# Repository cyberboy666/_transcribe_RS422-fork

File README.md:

# \_transcribe_RS422-fork\_

### midi to _rs422_ bridge - for performance control of other old video mixers and switchers

### a fork of the existing [_transcribe_](https://github.com/cyberboy666/_transcribe_) project to experiment with rs422 - an alternative serial protocol

as discussed in this [github issue](https://github.com/cyberboy666/_transcribe_/issues/7) - the basic idea for this fork is to replace the max232 ic on transcribe with a max485 ic and experiment with a alternative version that will output rs422 serial instead. 

ultimitately this fork could be merged into the mainline by way of a _transcribe_ circuit revision that allows both protocols or adds the option for this extension circuit to be connected

panasonic mx20 is an example of a video mixer that could be controlled over rs422 serial - it expects it over (the rather uncommon) mini-din socket

the panasonic mx50 i believe can take either rs232 or rs422 on its din9 sefrial socket (selectable by a switch) this could be a good way for me to test the circuit myself

## main _transcribe_ readme

<details><summary>readme from original version of _transcribe_</summary>

### midi to rs232 bridge - for performance control of old video mixers and switchers

- this circuit is distributed by __UNDERSCORES__ - _an open video hardware label_ : it is available to purchase - as a pcb, kit or assembled unit - at [underscores.shop](https://underscores.shop/_transcribe_/)
- the schematic for the circuit can be found [here](/hardware/schematic.pdf)
- the pcb gerber files for the lastest version can be found [here](/hardware/gerber_latest.zip)
- consider [donating](https://liberapay.com/underscores/) to the underscores project to help us continue creating for the commons

## description

people in the video-art community are performing with old hardware video-mixers such as the Pansonic_WJ_AVE55 and Pansonic_WJ_MX30/50. some of these mixers have a RS232 serial port for interfacing with them digitally. this is especially useful for live performance where sequencing can assist physical actions. there are some cool examples of software specifically written to interface with these mixers (such as [Freds excel app](https://a2m2.ch/fred/wj-ave55.htm) and  [Klifs MaxPatch](https://vimeo.com/161662975) ) , but there many more programs and devices that are made to interface digitally using MIDI.

the aim of this project is to create a small utility module that can __\_transcribe\___ _MIDI_, a protocol used commonly in live&performance instruments to the specific _RS-232 video-device specification_ , to better equip these retired workstations for their new life of glamour on stage

- input USB-midi from a USB-HOST such as a computer or rpi
- input serial-midi from older midi devices (din5)
- input USB-midi for a USB-DEVICE such as a korg nanokontroller or otherwise
- output RS232-serial commands over 3.5mm jack or dsub9 socket to control panasonic video-mixers and other devices
- all these interfaces are bi-directional and so can be modified with firmware to do other useful things (eg like a USB-DEVICE -> SERIAL midi converter)

## demo video

# documentation

this project is fully _open-source hardware_ - all the files required to build it are included in this repo for free. if you have the time and/or skill you can contribute back by collaborating on / testing new designs, improving these docs, making demo videos/other creative content etc. you can also support the project financially by [donating directing](https://liberapay.com/underscores/), or purchasing through the [web shop](https://underscores.shop).

depending on whether you are going fully diy or buying an assembled and tested unit, some of the following guides will be relavent to you. the flow would be:

## ordering parts

<details><summary><b>parts sourcing guide (w/ notes on pcb fabracation )</b> - start here if you are building fully from scatch or have purchased a pcb</summary>

i try to source all the parts i can from either:
- [tayda](https://www.taydaelectronics.com/) ; cheaper for common parts like resistors etc, also good for mechanical parts like switches and buttons
- [mouser](https://www.mouser.de/) ; has lots more options, speciality video ic's, can sometimes cost more (free shipping on orders over 50euros)
- other ; ocationally there will be parts which will need to be sourced elsewhere - usaully either aliexpress, ebay or amazon etc...

take a look at the [full_bom](/hardware/bom/full_bom.csv) for this project to see where i am sourcing each part from
  
## omitting parts
  
if you know exactly how you will use your _transcribe_ some parts of this circuit build can be omitted. the pcb is divided into sections that are marked on silk-screen:

- __A - micro-conntroller - centre__ : this is the brain of the circuit and is required to make it do anything. its also where USB_MIDI is received from(/sent to) usb-hosts (eg computer or raspberry pi)
- __B - rs232 serial - output(/input)__ : for sending(/receiving) serial at rs232 levels - only omit if you are not using this board for its default / intended purpose
- __C - serial midi - input(/output)__ : for receiving(/sending) midi messages over serial (usually on older hardware over din5 or 3.5mm jack) - can omit if you are only using (newer) hardware with USB-MIDI
- __D USB-midi HOST__: adds circuitry so that micro-controller can act as USB-HOST. for receiving midi messages from(/sending to) usb-devices (eg korg nanokontrol2) - can omit this if not interested in controlling from usb-devices

## import into tayda

- go to the [tayda quick order](https://www.taydaelectronics.com/quick-order/) and in bottom corner choose _add from file_
- select the file [tayda_bom.csv](../hardware/bom/tayda_bom.csv) in the BOM folder (you will have to download it first or clone this repo)
- after importing select _add to cart_
- __NOTE:__ the minimum value for resistors is 10, so you may need to modify these values to add to cart (or if they are already modified here you will need to see the  full_bom for actual part QTY) 

- OPTIONAL: it is a good idea to add some dip-ic sockets and 2.54pin headers/sockets to your tayda order if you dont have them around already
  
## import into mouser

- go to [mouser bom tool](https://nz.mouser.com/Bom/) and click _upload spreadsheet_
- select the file [mouser_bom.csv](../hardware/bom/mouser_bom.csv) in this folder (you will have to download it first or clone this repo), then _upload my spreadsheet_ and _next_
- ensure that __Mouser Part Number__ is selected in the dropdown above the first row, then _next_, _process_
- if everything looks correct can now put _add to basket_

# ordering pcbs

you can support this project by buying individual pcbs from the [shop](https://underscores.shop). if you would rather have pcbs fabricated from gerbers directly the file you need is [here](/hardware/gerber_latest.zip) 

- i get my pcbs fabricated from [jlcpcb](https://cart.jlcpcb.com/quote) - 5 is the minumum order per design
- upload the zip file with the `add gerber file` button
- the default settings are mostly fine - set the __PCB Qty__ and __PCB Color__ settings (you can check that the file looks correct with pcb veiwer)
- it may be best to combine orders with other pcbs you want to have fab'd since the shipping can cost more than the items - also orginising group buys is a good way to distribute the extra pcbs /costs 
  
i often use jlcpcb because they are reliable, cheap and give you an option of colours. remember though that the cheapest Chinese fab houses are not always the most ethical or environmently friendly - if you can afford it consider supporting local companies. 

</details>

## assembly guide

<details><summary><b>assembly guide</b> - start here if you have purchased a diy kit</summary>

## interactive BOM for build guiding

follow this link to view the [interactive BOM](https://htmlpreview.github.io/?https://github.com/cyberboy666/_transcribe_/blob/main/hardware/bom/ibom.html)

## general solder advices

- remember to heat pad first (2-3seconds), then add solder, then continue to heat (1-2seconds)

- Checkout the web-comic [soldering is easy](https://mightyohm.com/files/soldercomic/FullSolderComic_EN.pdf) for more soldering advice

## general order of assembly

- in general while assembling i start placing resistors and capacitors first. placing 5 - 10 components at a time and then flipping the board to solder them and trim the legs etc.
- next i would do diodes, transistors and ic's - taking care that these are placed in the right direction (using a ic socket can be useful)
- finally i place the interface parts - rca jacks, power jack, pots and switches - make sure these have lots of solder on for structural stablity

## interface choice / double footprint
  
_serial-midi_ is most commonly sent over __din5__ (older hardware) J5 & J7 or __trs 3.5mm jack__ (newer hardware) J4 & J6 - footprints for both are overlayed on the pcb so you can choose which one you would like to have
  
## Usb-host shield

__IMPORTANT: A trace needs to be cut on the usb-host-shield to allow it to be powered by 5v__ – _see the diagram below_ – this is best done with a craft knife – take care not to cut any other traces accidentally.

all pins on the outer vertical lines need to be soldered to the board. In addition to this the single topmost inner pin (labeled 5v in diagram) needs to be soldered to pcb also
  
## specific assembly advice

Start by soldering the smallest parts first: resistors, diodes, capacitors and regulators - take note of the direction on the diodes - black bar on component matching black bar on footprint

Next lets do the ic’s/sockets - make sure the direction is correct! place in and fold two corner pins to hold in place, then solder all pins. you can place the ic in now too

Now lets do the micro-controller and usb-host-shield - if you want to be able to remove them from the board you will need to solder header sockets to the board first – otherwise can directly solder the header pins

for the usb-host-shield right_row I would do a 1x2 header horizontally at the top to catch that 5v pin and then 1x11 row vertically for the rest – the left_row can just be a single 1x12 vertical header

Finally place the interface parts (eg jacks and sockets) be generous with the solder here -> this is to strengthen the mechanical connections as well as making electrical ones

Leave j8 header unpopulated – this just exposes the bootloader pins so firmware can be reset in the rare case that the pro-micro gets bricked – also leave j1 header unpopulated unless you want to power from a euro-power-header
  
</details>

## firmware guide

<details><summary><b>firmware guide</b> - for editing the code & flashing it to your micro-controller</summary>
  
## flashing firmware onto the micro-controller
  
if you have got a kit from the shop the default firmware will be pre-configured - still you probably will want to follow this so you can edit the code and update the mappings.
  
### install guide
  
all _underscores_ projects with micro-controllers use [platformio](https://platformio.org/) with [visual studio code](https://code.visualstudio.com/) to edit, flash and monitor the code.
  
- first download (and unzip) the code in this repo - easiest is [as a zip](https://github.com/cyberboy666/_transcribe_/archive/refs/heads/main.zip) or you can clone using git if you are comfortable with this
- next download, install and open [visual studio code](https://code.visualstudio.com/#alt-downloads)
- now open the extension tab within vscode on left vertical menu (or press ctrl-shift-x) and search for `platformio` to install this extension

- connect the micro-controller to computer via usb, open the _transcribe_ software folder (ctrl-k ctrl-o) in vscode and find the _platformio_ commands (either in left vertical menu under _platformio_ or little tick/arrow symbols along bottom blue bar) - `PlatformIO: Upload` should flash the default code to your micro-controller

### mapping edit guide
  
this guide is just an overview to get you started. the two files that you might want to look at are: 
- [software/src/commands.h](software/src/commands.h) - where the specific serial protocol commands are defined
- [software/src/main.cpp](software/src/main.cpp) - all the code that handles receiving midi and writing serial is - including the _mapping function_
  
open the `src/main.cpp` file in vscode and fold all functions by pressing `ctrl-k, ctrl-0` - this makes reading it a bit easier:

open and take a look at the `setAVE55nanokontrolMap` method - we will first look at these lines:
  
```cpp
    else if(midiParam1 == 64){setCmd(A55_A_BUS_SOURCE_1);}
    else if(midiParam1 == 65){setCmd(A55_A_BUS_SOURCE_2);}
```
  
the first line is saying: __if the incoming midi message has `midiParam1` set to 64, then send the `A55_A_BUS_SOURCE_1` command over rs232 serial__ - since we can see from above that this line is within the conditional: `if(midiCommand == MIDICOMMAND::CC)` , then we know that `midiParam1` is refering to the cc channel. we can also see in the __commands.h__ file  that `A55_A_BUS_SOURCE_1` is set to the command from that panasonic ave55 specification that switches the a-bus source to input 1:
```cpp
  #define A55_A_BUS_SOURCE_1 "VCP:200"
```

this line is mapping a midi message on cc channel 64 to the rs232 message for ave55 that switches the input source. this is the simplest kind of mapping - a discrete BUTTON press. however there are also mappings to functions that take parameter values also. for example the `A55_A_B_MIX_LEVEL` command that wipes between the a-bus to b-bus on the mixer:
  
 ```cpp
 if(midiParam1 == 0){setCmd(A55_A_B_MIX_LEVEL, midiParam2);}
 else if(midiParam1 == 1){setCmd(A55_THRESHOLD_LUM_KEY, midiParam2);}
 else if(midiParam1 == 2){setCmd(A55_CENTER_WIPE_X, midiParam2);}
 else if(midiParam1 == 3){setCmd(A55_CENTER_WIPE_Y, midiParam2);}
```

we can see that on these mappings also the __midiParam2__ value is passed into the _setCmd_ function - this is the _cc value_ of the channel - on my controller - the position of the slider that is sending on cc channel 0. the rs232 command for this function also takes a varible input to set position of the mix:
```cpp
#define A55_A_B_MIX_LEVEL "VMM:179~0"
```
where the `~0` is a placeholder that is replaced with the hex-converted value of `midiParam2`. there are other ways to map midi notes to rs232 commands. there are more 'advanced' mapping functions in the code for this - for example:
```cpp
else if(midiParam1 == 35){setCmdParamRandom(A55_A_B_MIX_LEVEL);}
```
takes a button press and converts it to a random mix level. another useful mapping is taking continuous inputn (eg slider on midi controller)  and convert this to a STEP of different discrete commands - for example:
```cpp
else if(midiParam1 == 17){setCmdStepAVE55(A55_A_BUS_MOSAIC_OFF, midiParam2, 76, 6);}
else if(midiParam1 == 18){setCmdStepAVE55(A55_A_BUS_PAINT_OFF, midiParam2, 82, 6);}
```
these mappings STEP between sending 6 different rs232 commands on a single slider - so you can set all the mosaic/paint effect levels in one turn. another useful 'advanced' mapping function is the SWITCH:
  
```cpp
else if(midiParam1 == 50){setCmdSwitch(MX50_A_BUS_EFFECT_ON, MX50_A_BUS_EFFECT_OFF, 3);}
```

this will SWITCH between sending the _on_ and _off_ commands when the same midi command is send (the third parameter input `3` is a unique index reference to store the on/off state in memory between messages)
  
these are just some examples of the ways that code can be used to perform these mappings. if you are interested can see more in the code directly or write your own mapping functions!

</details>
  
## operating guide
  
<details><summary><b>operating guide</b> - start here if you have purchased an assembled unit</summary>

</details>

### more info

<details><summary><b>how the circuit works</b></summary>
  
[coming soon]
                                                                                                                             
</details>

<details><summary><b>contributing guide</b></summary>
  
if you would like to contribute back to these projects in some way but dont know how the best thing (for now) would be to reach out to me directly ( tim@cyberboy666.com or @cyberboy666 on scanlines forum) - i will be happy to help
  
</details>

## credits & more info

This circuit is distributed through UNDERSCORES – open video hardware label – visit [underscores.shop](https://underscores.shop) for more info

The pcb was designed using KICAD

Everything from gerbers, cad files, panels and documentation is freely available online and distributed under CC-BY-SA / open-source licenses – help us contribute to the commons !

Ask any questions or start discussions related to this project on the [scanlines.xyz](https://scanlines.xyz) forum – an online community space dedicated to diy av / electronic media art

You can contact me directly at tim (at) cyberboy666 (dot) com 
Please get in touch if you are interested in hosting a workshop !

Thanks to Gilbert Sinnott for helping with initial experiments. to Bastien Lavaud for circuit advice, always. To Ben Caldwell for project advice. To everyone who has or will contribute ♥♥♥

</details>

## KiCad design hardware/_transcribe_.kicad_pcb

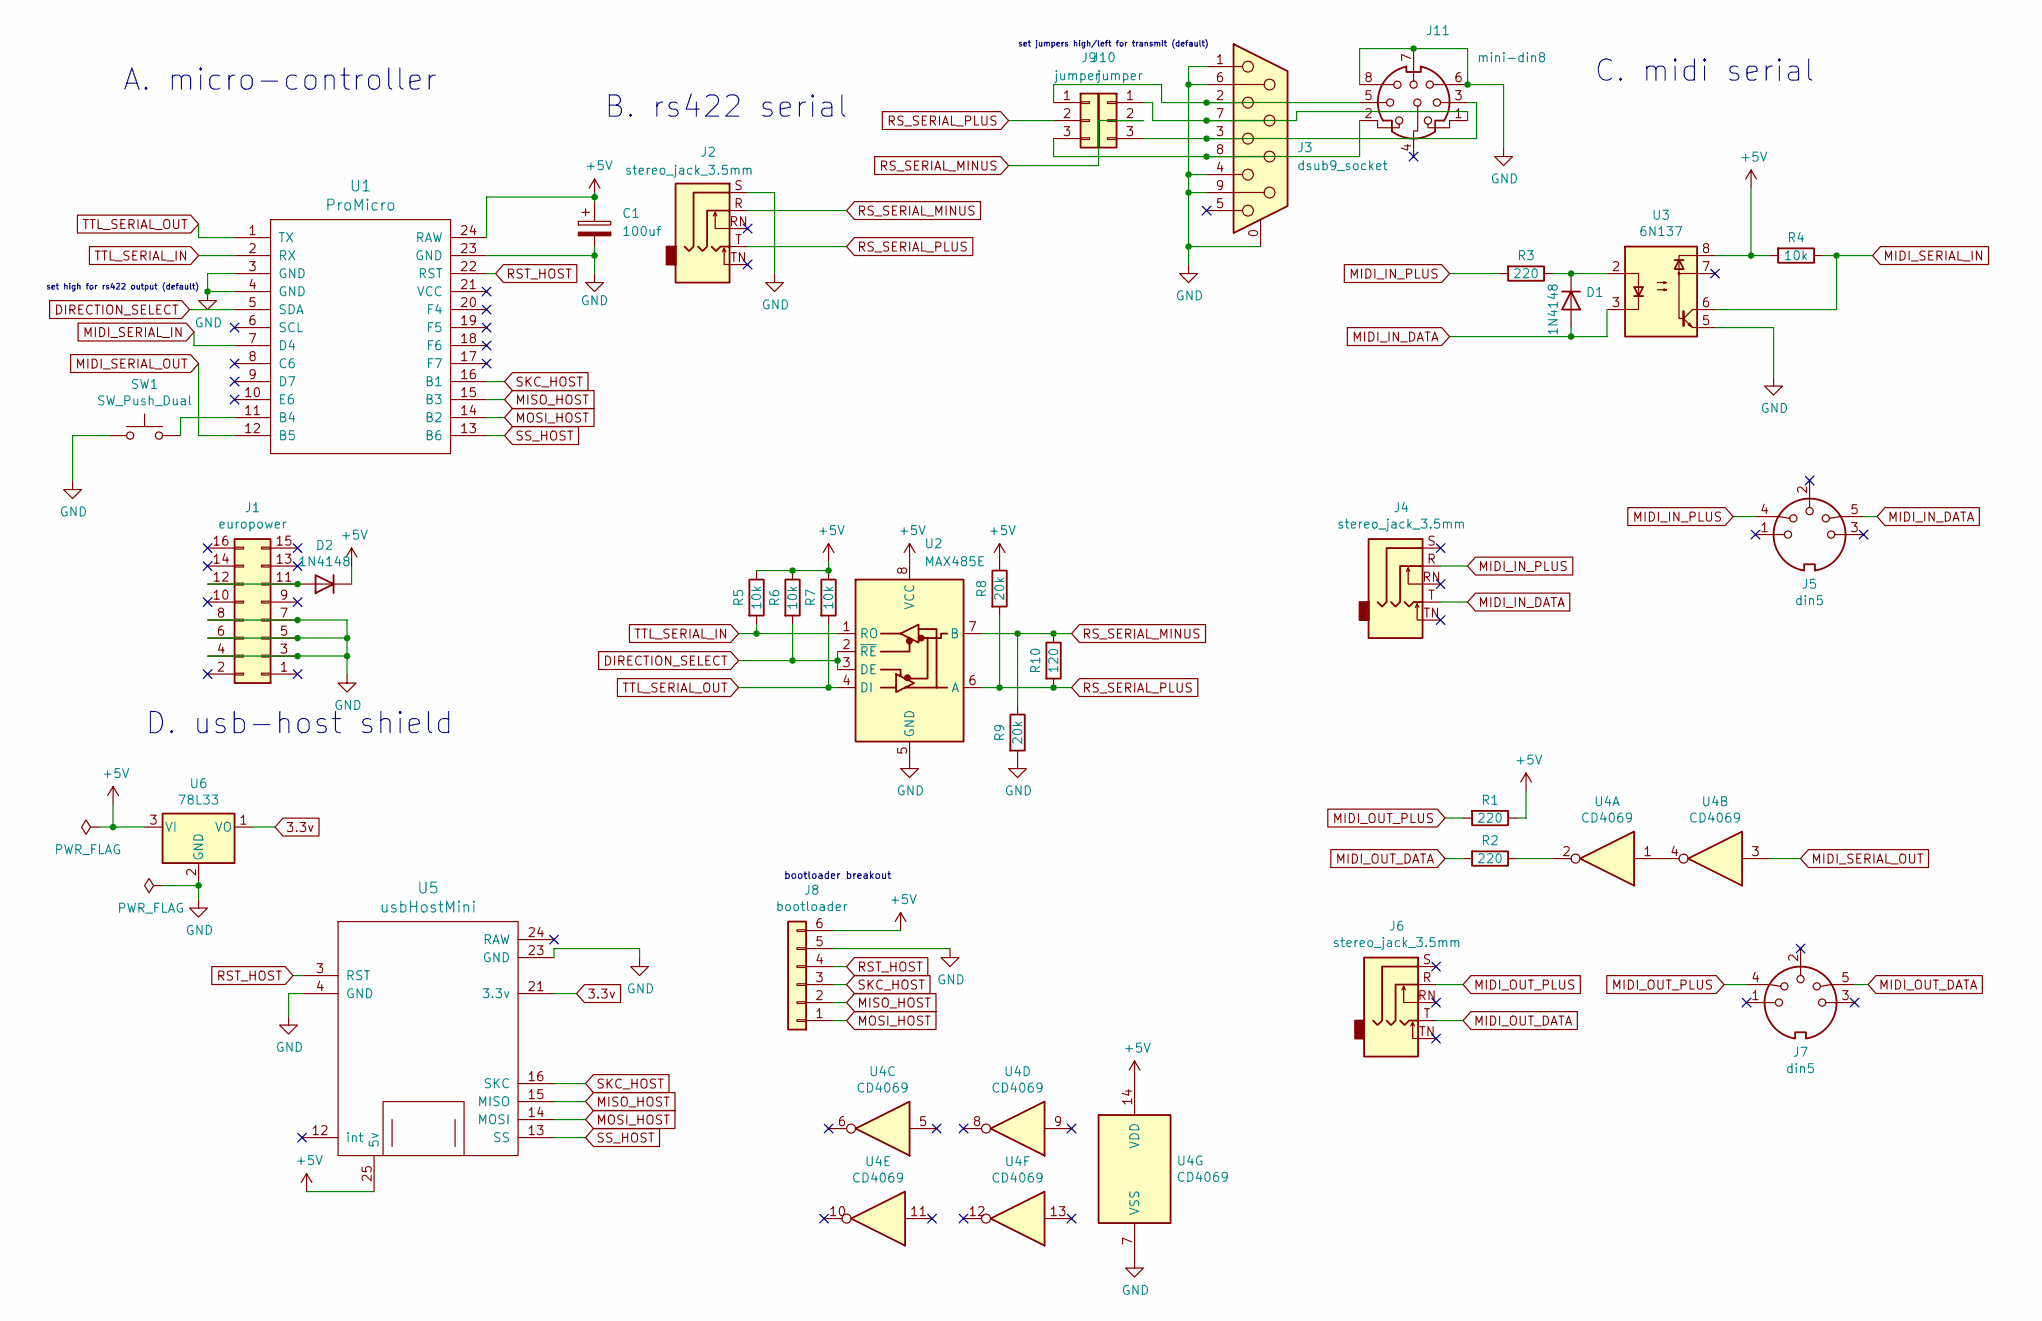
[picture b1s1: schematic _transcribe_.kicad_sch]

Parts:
C1: 100uf; CP_Radial_D5.0mm_P2.50mm
D1, D2: 1N4148; D_T-1_P5.08mm_Horizontal
J1: europower; PinHeader_2x08_P2.54_Euro
J2, J4, J6: stereo_jack_3.5mm; horizontal_3.5mm_stereo_TRS_jack_A-853
J3: dsub9_socket; tht_DSUB-9_Vertical_Tayda
J5, J7: din5; horizontal_din5-A1010
J8: bootloader; PinSocket_1x06_P2.54mm_Vertical
J9, J10: jumper; PinSocket_1x03_P2.54mm_Vertical
J11: mini-din8; CUI_MD-80SV
R1, R2, R3: 220; R_Axial_DIN0207_L6.3mm_D2.5mm_P5.08mm_Vertical
R4, R5, R6, R7: 10k; R_Axial_DIN0207_L6.3mm_D2.5mm_P5.08mm_Vertical
R8, R9: 20k; R_Axial_DIN0207_L6.3mm_D2.5mm_P5.08mm_Vertical
R10: 120; R_Axial_DIN0207_L6.3mm_D2.5mm_P5.08mm_Vertical
SW1: SW_Push_Dual; SW_PUSH_6mm_H7.3mm
U1: ProMicro
U2: MAX485E; DIP-8_W7.62mm_LongPads
U3: 6N137; DIP-8_W7.62mm
U4: CD4069; DIP-14_W7.62mm
U5: usbHostMini; usbHostMidi
U6: 78L33; TO-92_HandSolder

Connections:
3.3v: U5.21 (3.3v), U6.1 (VO)
+5V: C1.1, D2.1 (K), J8.6, R1.1, R4.2, R5.1, R6.1, R7.1, R8.1, U1.24 (RAW), U2.8 (VCC), U3.8, U4.14 (VDD), U5.25 (5v), U6.3 (VI)
DIRECTION_SELECT: R6.2, U1.5 (SDA), U2.2 (~RE), U2.3 (DE)
GND: C1.2, J1.3, J1.4, J1.5, J1.6, J1.7, J1.8, J2.S, J3.0 (PAD), J3.1, J3.4, J3.6, J3.9, J8.5, J11.6, J11.7, J11.8, R9.2, SW1.1, U1.3 (GND), U1.4 (GND), U1.23 (GND), U2.5 (GND), U3.5, U4.7 (VSS), U5.4 (GND), U5.23 (GND), U6.2 (GND)
MIDI_IN_DATA: D1.2 (A), J4.T, J5.5, U3.3
MIDI_IN_PLUS: J4.R, J5.4, R3.2
MIDI_OUT_DATA: J6.T, J7.5, R2.2
MIDI_OUT_PLUS: J6.R, J7.4, R1.2
MIDI_SERIAL_IN: R4.1, U1.7 (D4), U3.6
MIDI_SERIAL_OUT: U1.12 (B5), U4.3
MISO_HOST: J8.2, U1.15 (B3), U5.15 (MISO)
MOSI_HOST: J8.1, U1.14 (B2), U5.14 (MOSI)
unnamed: D1.1 (K), R3.1, U3.2
unnamed: D2.2 (A), J1.11, J1.12
unnamed: J3.2, J9.1, J11.5
unnamed: J3.8, J9.3, J11.2
unnamed: J3.7, J10.1, J11.1
unnamed: J3.3, J10.3, J11.3
unnamed: R2.1, U4.2
unnamed: SW1.2, U1.11 (B4)
unnamed: U4.1, U4.4
RST_HOST: J8.4, U1.22 (RST), U5.3 (RST)
RS_SERIAL_MINUS: J2.R, J10.2, R9.1, R10.1, U2.7 (B)
RS_SERIAL_PLUS: J2.T, J9.2, R8.2, R10.2, U2.6 (A)
SKC_HOST: J8.3, U1.16 (B1), U5.16 (SKC)
SS_HOST: U1.13 (B6), U5.13 (SS)
TTL_SERIAL_IN: R5.2, U1.2 (RX), U2.1 (RO)
TTL_SERIAL_OUT: R7.2, U1.1 (TX), U2.4 (DI)

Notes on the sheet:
A. micro-controller
bootloader breakout
B. rs422 serial
set jumpers high/left for transmit (default)
set high for rs422 output (default)
D. usb-host shield
C. midi serial

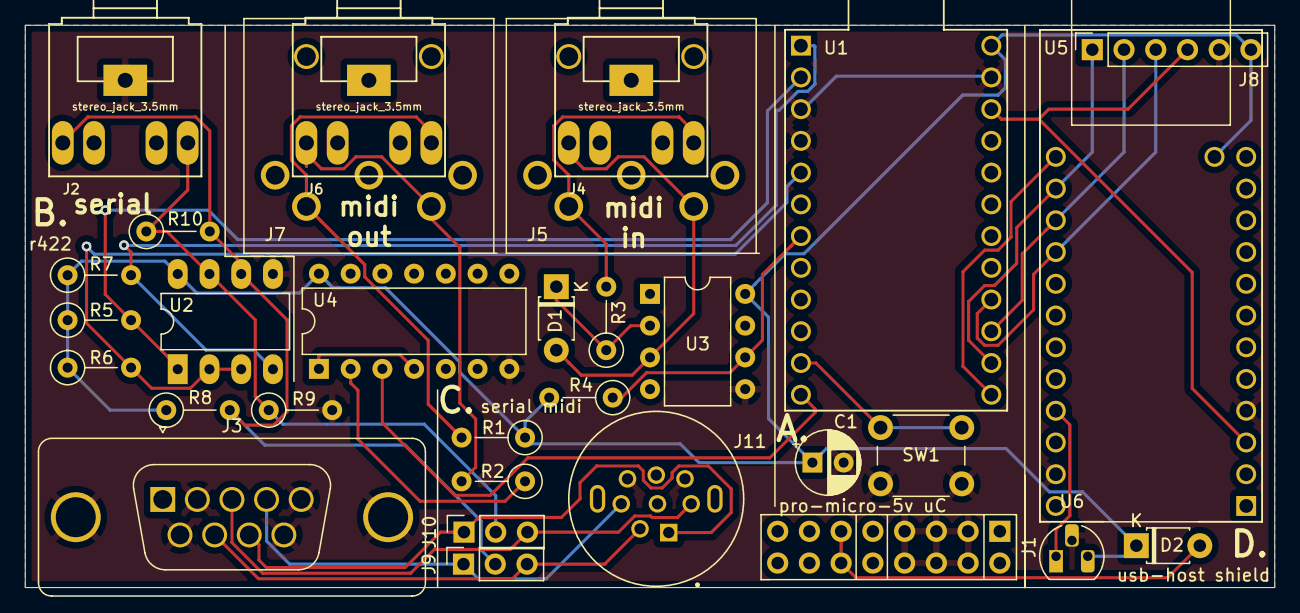
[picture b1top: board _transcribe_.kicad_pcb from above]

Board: 2 copper layers, 100.0 x 45.0 mm, 31 parts (0 on the bottom side), 28 nets.

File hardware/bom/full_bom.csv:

sku,qty,ref,val,vendor
A-959,1,C1 ,100uf,tayda
A-157,2,D1 D2 ,1N4148,tayda
A-2956,1,J1 ,europower,tayda
-,1,J11 ,mini-din8
A-853,3,J2 J4 J6 ,stereo_jack_3.5mm,tayda
A-300,1,J3 ,dsub9_socket,tayda
A-1010,2,J5 J7 ,din5,tayda
-,1,J8 ,bootloader
A-1324,2,J9 J10 ,jumper,tayda
A-2246,3,R1 R2 R3 ,220,tayda
-,1,R10 ,120
A-2203,4,R4 R5 R6 R7 ,10k,tayda
-,2,R8 R9 ,20k
A-5129,1,SW1 ,SW_Push_Dual,tayda
-,1,U1 ,ProMicro
A-712,1,U2 ,MAX485E,tayda
A-871,1,U3 ,6N137,tayda
A-882,1,U4 ,CD4069,tayda
-,1,U5 ,usbHostMini
A-492,1,U6 ,78L33,tayda

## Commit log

2022-06-22 replace rs232 with rs422 parts in schem and pcb
2022-08-11 finished v0_1 first protoytpe

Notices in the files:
README.md:
Everything from gerbers, cad files, panels and documentation is freely available online and distributed under CC-BY-SA / open-source licenses – help us contribute to the commons !
hardware/_transcribe_.kicad_pcb:
CC-BY-SA
